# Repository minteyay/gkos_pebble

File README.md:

# wireless GKOS chording keyboard + mouse with BLE

based on the GKOS chording standard (http://gkos.com/gkos/gkos-charset.html) with a few modifications for computer-centric usage.

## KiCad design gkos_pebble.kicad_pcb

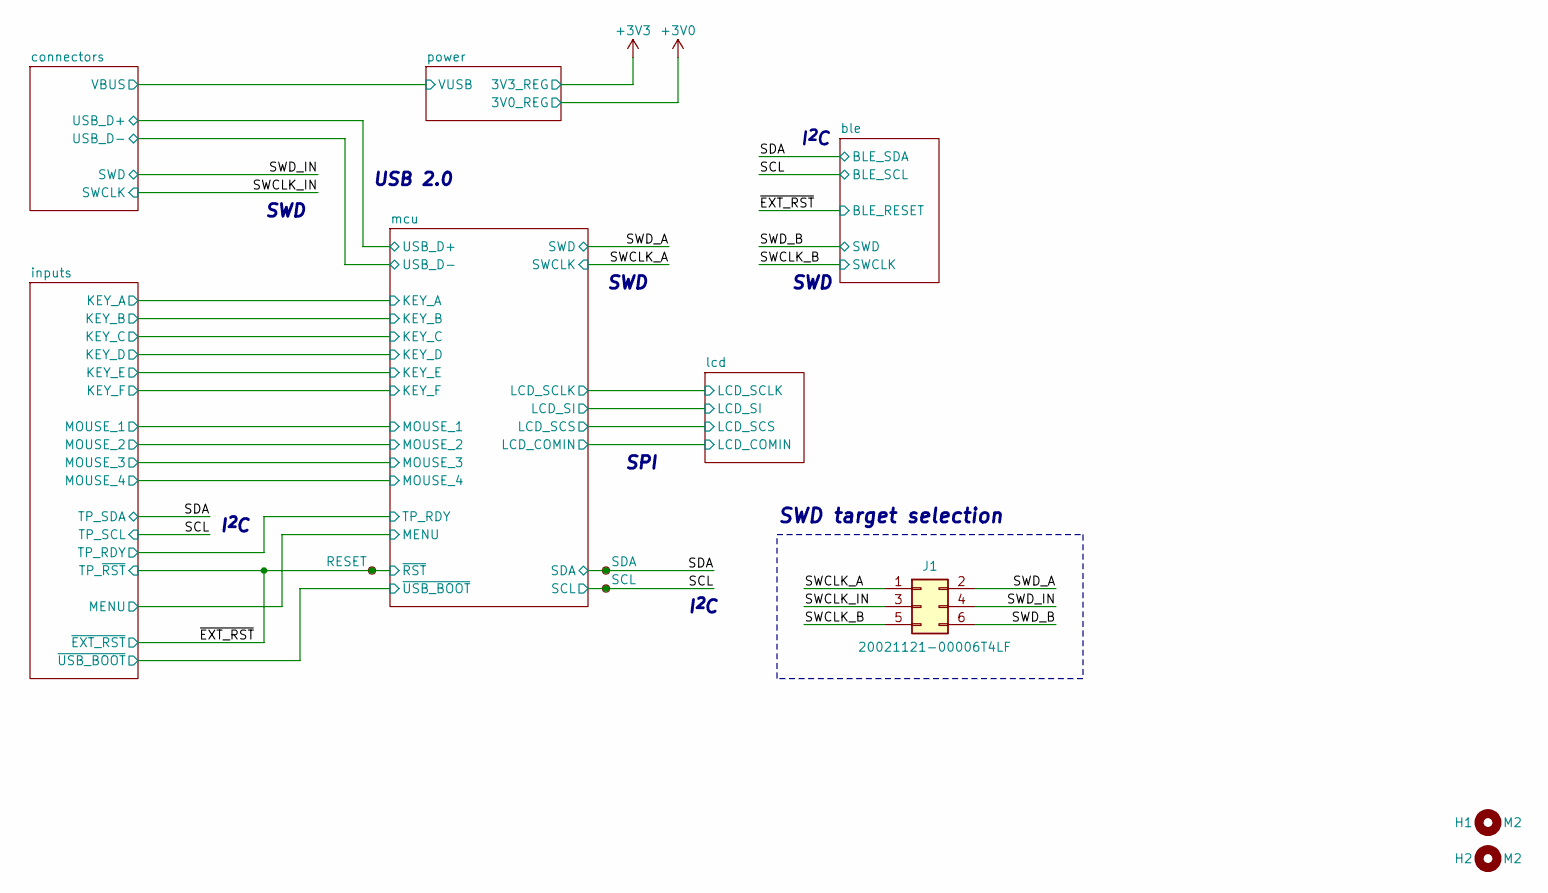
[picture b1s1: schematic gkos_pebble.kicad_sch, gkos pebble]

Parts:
H1, H2: M2; MountingHole_2.2mm_M2
J1: 20021121-00006T4LF; PinHeader_2x03_P1.27mm_Vertical_SMD
TP1: RESET; TestPoint_Pad_D1.0mm
TP2: SDA; TestPoint_Pad_D1.0mm
TP3: SCL; TestPoint_Pad_D1.0mm

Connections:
/SCL: TP3.1; also elsewhere on the board
/SDA: TP2.1; also elsewhere on the board
/SWCLK_A: J1.1; also elsewhere on the board
/SWCLK_B: J1.5; also elsewhere on the board
/SWCLK_IN: J1.3; also elsewhere on the board
/SWD_A: J1.2; also elsewhere on the board
/SWD_B: J1.6; also elsewhere on the board
/SWD_IN: J1.4; also elsewhere on the board
/~EXT_RST: TP1.1; also elsewhere on the board

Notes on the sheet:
SWD
I^{2}C
SPI
USB 2.0
SWD target selection

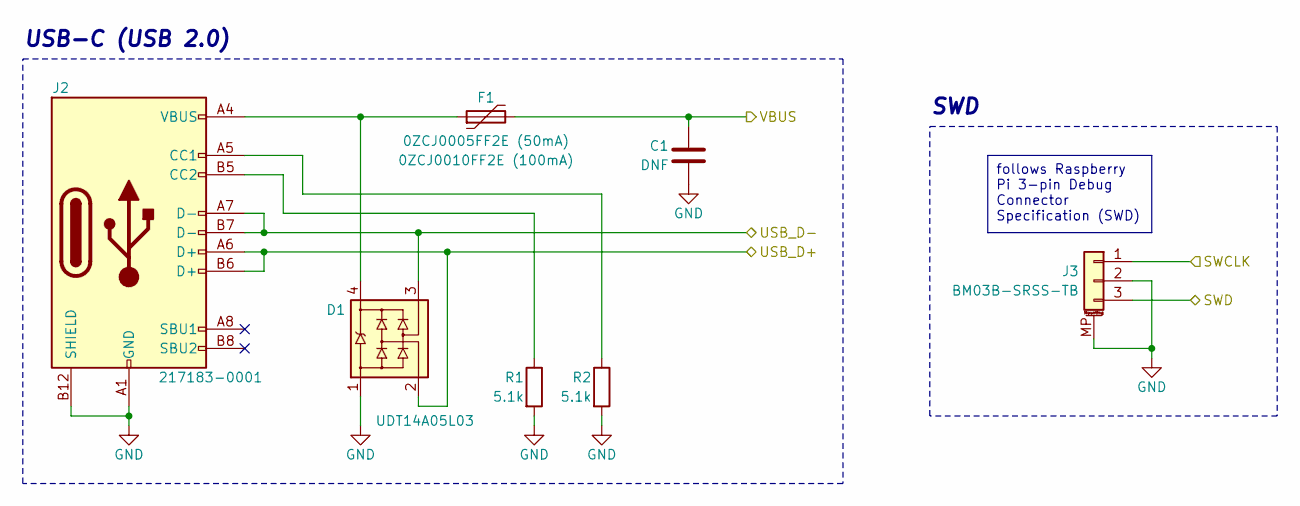
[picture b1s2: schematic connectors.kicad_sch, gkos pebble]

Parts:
C1: DNF; C_0603_1608Metric
D1: UDT14A05L03; SOT-143_Handsoldering
F1: 0ZCJ0005FF2E (50mA); R_1206_3216Metric
J2: 217183-0001; 2171830001
J3: BM03B-SRSS-TB; JST_SH_BM03B-SRSS-TB_1x03-1MP_P1.00mm_Vertical
R1, R2: 5.1k; R_0603_1608Metric

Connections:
/SWCLK_IN: J3.1; also elsewhere on the board
/SWD_IN: J3.3; also elsewhere on the board
/connectors/VBUS: C1.1, F1.2; also elsewhere on the board
/mcu/USB_D+: D1.2, J2.A6 (D+), J2.B6 (D+); also elsewhere on the board
/mcu/USB_D-: D1.3, J2.A7 (D-), J2.B7 (D-); also elsewhere on the board
GND: C1.2, D1.1, J2.A1 (GND), J2.A12 (GND), J2.B1 (GND), J2.B12 (GND), J3.2, J3.MP (MountPin), R1.2, R2.2; also elsewhere on the board
unnamed: D1.4, F1.1, J2.A4 (VBUS), J2.A9 (VBUS), J2.B4 (VBUS), J2.B9 (VBUS)
unnamed: J2.A5 (CC1), R2.1
unnamed: J2.B5 (CC2), R1.1

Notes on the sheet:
follows Raspberry Pi 3-pin Debug Connector Specification (SWD)
SWD
USB-C (USB 2.0)

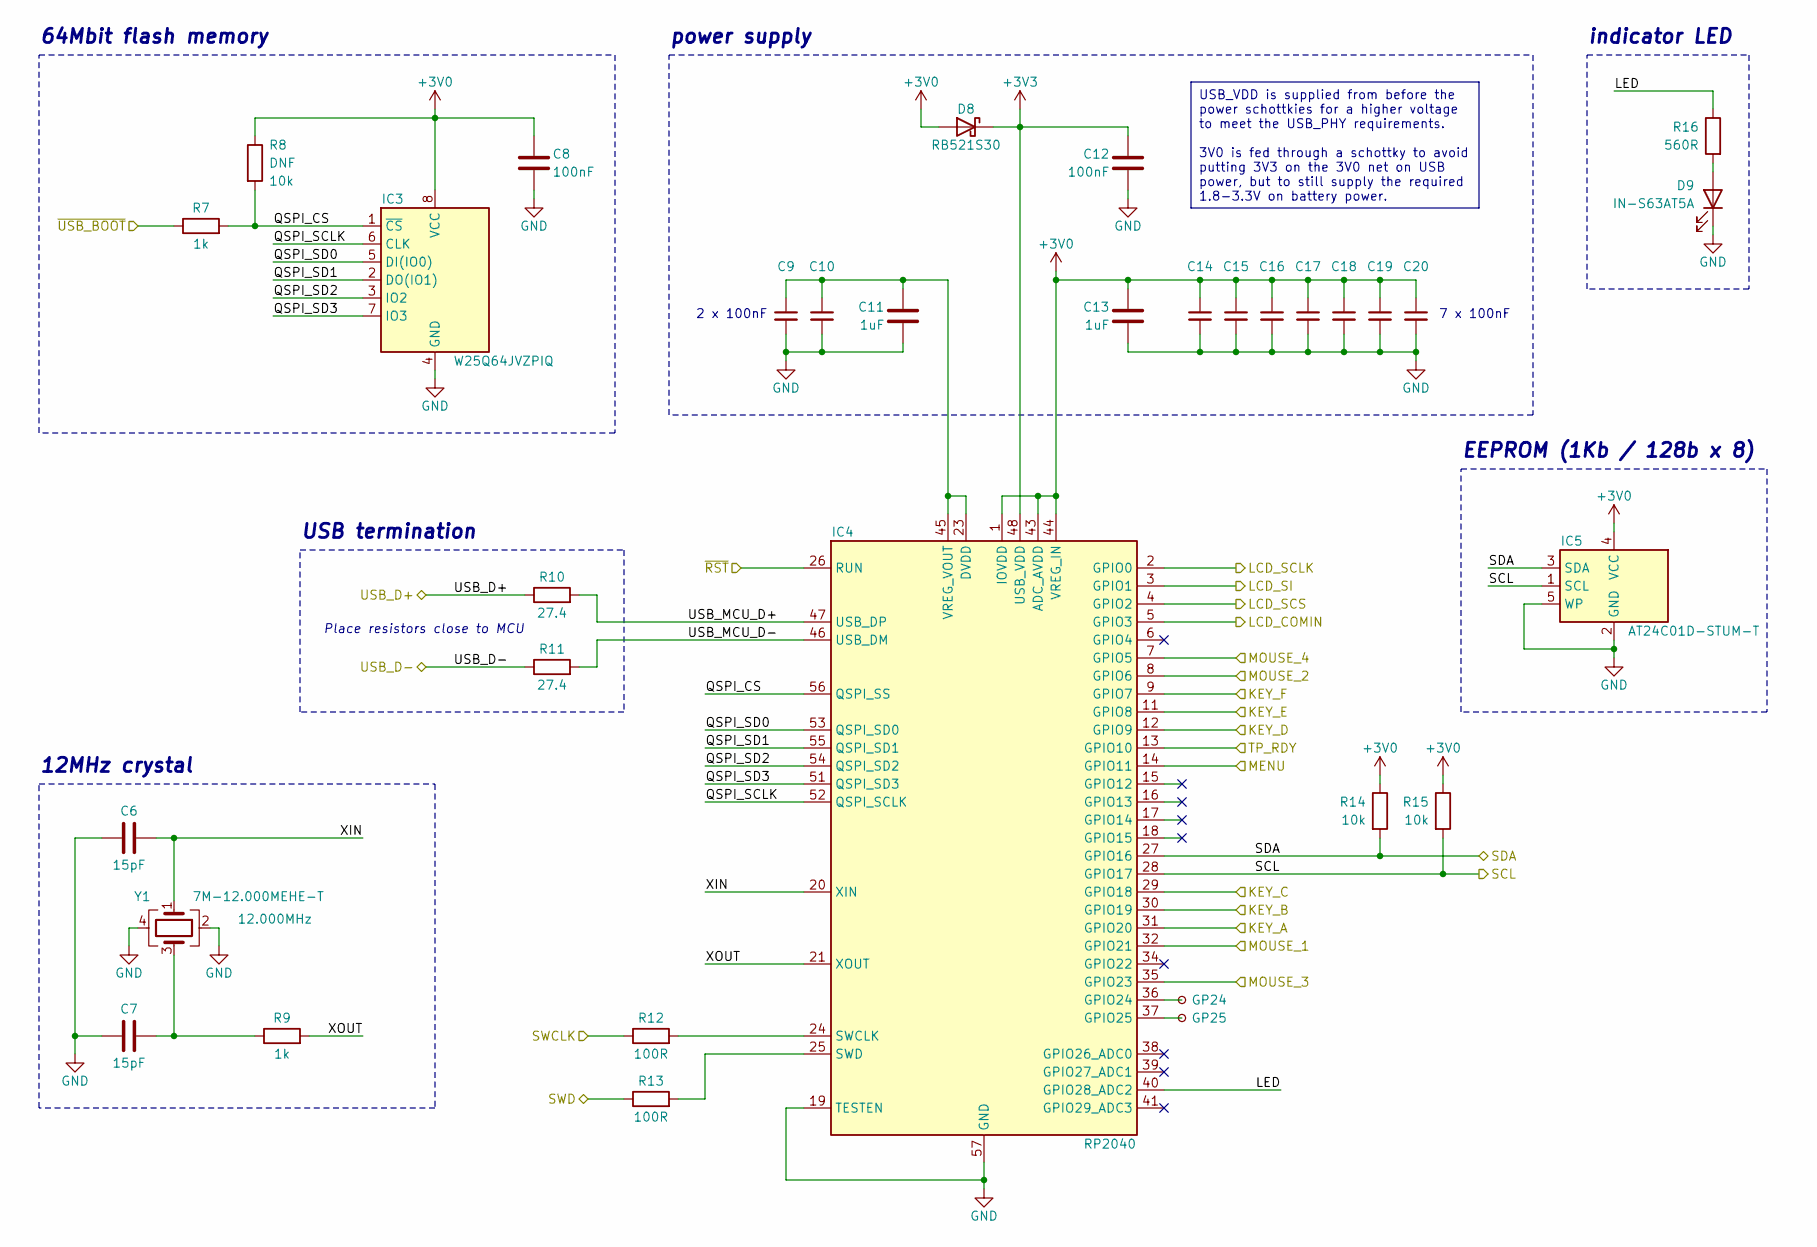
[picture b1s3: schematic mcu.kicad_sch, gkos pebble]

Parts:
C6, C7: 15pF; C_0402_1005Metric
C8: 100nF; C_0603_1608Metric
C9, C10, C12, C14, C15, C16, C17, C18, C19, C20: 100nF; C_0402_1005Metric
C11, C13: 1uF; C_0402_1005Metric
D8: RB521S30; D_SOD-523
D9: IN-S63AT5A; LED_0603_1608Metric
IC3: W25Q64JVZPIQ; WSON-8-1EP_6x5mm_P1.27mm_EP3.4x4.3mm
IC4: RP2040; QFN-56-1EP_7x7mm_P0.4mm_EP3.2x3.2mm
IC5: AT24C01D-STUM-T; SOT-23-5
R7: 1k; R_0603_1608Metric
R8: DNF; R_0603_1608Metric
R9: 1k; R_0402_1005Metric
R10, R11: 27.4; R_0402_1005Metric
R12, R13: 100R; R_0402_1005Metric
R14, R15: 10k; R_0402_1005Metric
R16: 560R; R_0603_1608Metric
TP4: GP24; TestPoint_Pad_D1.0mm
TP5: GP25; TestPoint_Pad_D1.0mm
Y1: 7M-12.000MEHE-T

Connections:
+3V0: C8.1, C13.1, C14.1, C15.1, C16.1, C17.1, C18.1, C19.1, C20.1, D8.2 (A), IC3.8 (VCC), IC4.1 (IOVDD), IC4.10 (IOVDD), IC4.22 (IOVDD), IC4.33 (IOVDD), IC4.42 (IOVDD), IC4.43 (ADC_AVDD), IC4.44 (VREG_IN), IC4.49 (IOVDD), IC5.4 (VCC), R8.1, R14.1, R15.1; also elsewhere on the board
+3V3: C12.1, D8.1 (K), IC4.48 (USB_VDD); also elsewhere on the board
/SCL: IC4.28 (GPIO17), IC5.1 (SCL), R15.2; also elsewhere on the board
/SDA: IC4.27 (GPIO16), IC5.3 (SDA), R14.2; also elsewhere on the board
/SWCLK_A: R12.1; also elsewhere on the board
/SWD_A: R13.1; also elsewhere on the board
/inputs/KEY_A: IC4.31 (GPIO20); also elsewhere on the board
/inputs/KEY_B: IC4.30 (GPIO19); also elsewhere on the board
/inputs/KEY_C: IC4.29 (GPIO18); also elsewhere on the board
/inputs/KEY_D: IC4.12 (GPIO9); also elsewhere on the board
/inputs/KEY_E: IC4.11 (GPIO8); also elsewhere on the board
/inputs/KEY_F: IC4.9 (GPIO7); also elsewhere on the board
/inputs/MENU: IC4.14 (GPIO11); also elsewhere on the board
/inputs/MOUSE_1: IC4.32 (GPIO21); also elsewhere on the board
/inputs/MOUSE_2: IC4.8 (GPIO6); also elsewhere on the board
/inputs/MOUSE_3: IC4.35 (GPIO23); also elsewhere on the board
/inputs/MOUSE_4: IC4.7 (GPIO5); also elsewhere on the board
/inputs/TP_RDY: IC4.13 (GPIO10); also elsewhere on the board
/inputs/~USB_BOOT: R7.1; also elsewhere on the board
/lcd/LCD_COMIN: IC4.5 (GPIO3); also elsewhere on the board
/lcd/LCD_SCLK: IC4.2 (GPIO0); also elsewhere on the board
/lcd/LCD_SCS: IC4.4 (GPIO2); also elsewhere on the board
/lcd/LCD_SI: IC4.3 (GPIO1); also elsewhere on the board
/mcu/LED: IC4.40 (GPIO28_ADC2), R16.1
/mcu/QSPI_CS: IC3.1 (~CS), IC4.56 (QSPI_SS), R7.2, R8.2
/mcu/QSPI_SCLK: IC3.6 (CLK), IC4.52 (QSPI_SCLK)
/mcu/QSPI_SD0: IC3.5 (DI(IO0)), IC4.53 (QSPI_SD0)
/mcu/QSPI_SD1: IC3.2 (DO(IO1)), IC4.55 (QSPI_SD1)
/mcu/QSPI_SD2: IC3.3 (IO2), IC4.54 (QSPI_SD2)
/mcu/QSPI_SD3: IC3.7 (IO3), IC4.51 (QSPI_SD3)
/mcu/USB_D+: R10.1; also elsewhere on the board
/mcu/USB_D-: R11.1; also elsewhere on the board
/mcu/USB_MCU_D+: IC4.47 (USB_DP), R10.2
/mcu/USB_MCU_D-: IC4.46 (USB_DM), R11.2
/mcu/XIN: C6.2, IC4.20 (XIN), Y1.1
/mcu/XOUT: IC4.21 (XOUT), R9.2
/~EXT_RST: IC4.26 (RUN); also elsewhere on the board
GND: C6.1, C7.1, C8.2, C9.2, C10.2, C11.2, C12.2, C13.2, C14.2, C15.2, C16.2, C17.2, C18.2, C19.2, C20.2, D9.1 (K), IC3.4 (GND), IC4.19 (TESTEN), IC4.57 (GND), IC5.2 (GND), IC5.5 (WP), Y1.2, Y1.4; also elsewhere on the board
unnamed: C7.2, R9.1, Y1.3
unnamed: D9.2 (A), R16.2
unnamed: IC4.36 (GPIO24), TP4.1
unnamed: IC4.37 (GPIO25), TP5.1
unnamed: IC4.24 (SWCLK), R12.2
unnamed: IC4.25 (SWD), R13.2
unnamed: C9.1, C10.1, C11.1, IC4.23 (DVDD), IC4.45 (VREG_VOUT), IC4.50 (DVDD)

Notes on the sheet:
USB_VDD is supplied from before the power schottkies for a higher voltage to meet the USB_PHY requirements. 3V0 is fed through a schottky to avoid putting 3V3 on the 3V0 net on USB power, but to still supply the required 1.8-3.3V on battery power.
Place resistors close to MCU
7 x 100nF
2 x 100nF
EEPROM (1Kb / 128b x 8)
indicator LED
USB termination
64Mbit flash memory
12MHz crystal
power supply

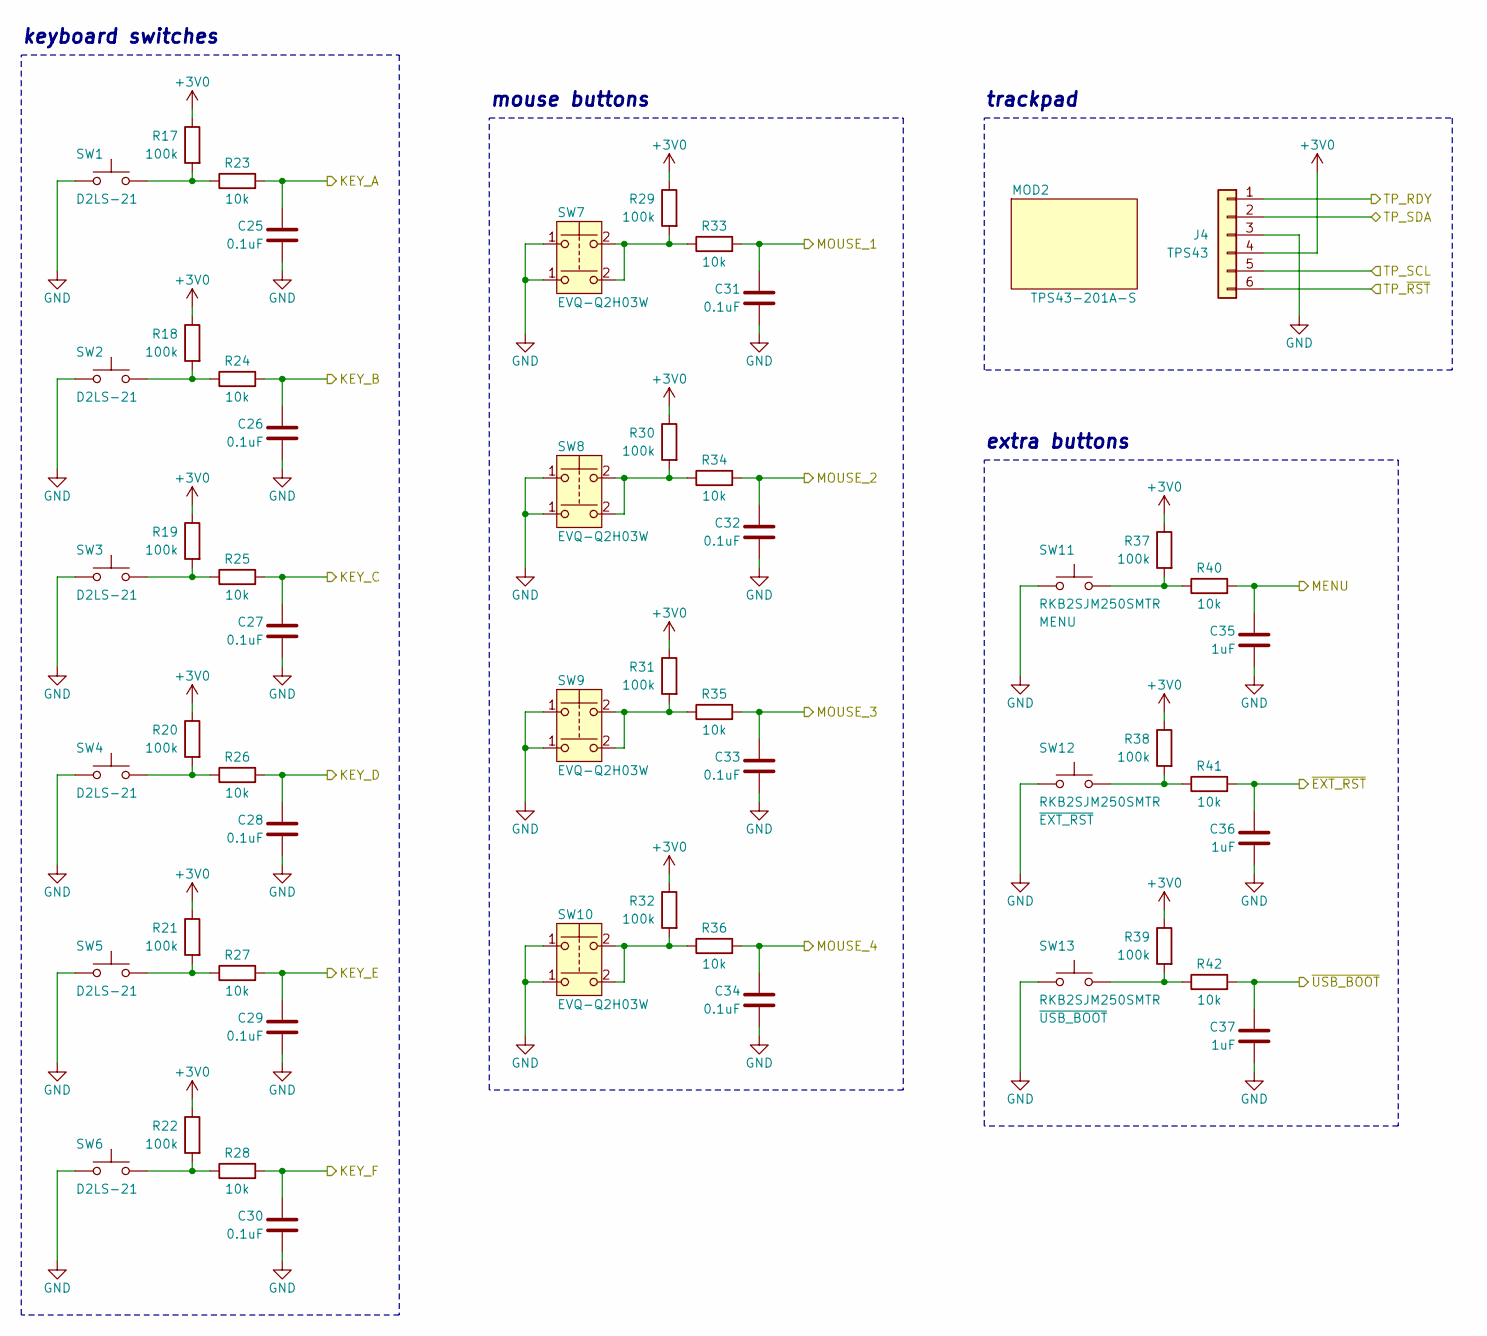
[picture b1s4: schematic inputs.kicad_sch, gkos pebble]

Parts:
C25, C26, C27, C28, C29, C30, C31, C32, C33, C34: 0.1uF; C_0603_1608Metric
C35, C36, C37: 1uF; C_0603_1608Metric
J4: TPS43; TPS43_wires
MOD2: TPS43-201A-S; TPS43
R17, R18, R19, R20, R21, R22, R29, R30, R31, R32, R37, R38, R39: 100k; R_0603_1608Metric
R23, R24, R25, R26, R27, R28, R33, R34, R35, R36, R40, R41, R42: 10k; R_0603_1608Metric
SW1, SW2, SW3, SW4, SW5, SW6: D2LS-21; D2LS
SW7, SW8, SW9, SW10: EVQ-Q2H03W
SW11, SW12, SW13: RKB2SJM250SMTR; RKB2SJM250SMTRLFS

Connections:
+3V0: J4.4, R17.1, R18.1, R19.1, R20.1, R21.1, R22.1, R29.1, R30.1, R31.1, R32.1, R37.1, R38.1, R39.1; also elsewhere on the board
/SCL: J4.5; also elsewhere on the board
/SDA: J4.2; also elsewhere on the board
/inputs/KEY_A: C25.1, R23.2; also elsewhere on the board
/inputs/KEY_B: C26.1, R24.2; also elsewhere on the board
/inputs/KEY_C: C27.1, R25.2; also elsewhere on the board
/inputs/KEY_D: C28.1, R26.2; also elsewhere on the board
/inputs/KEY_E: C29.1, R27.2; also elsewhere on the board
/inputs/KEY_F: C30.1, R28.2; also elsewhere on the board
/inputs/MENU: C35.1, R40.2; also elsewhere on the board
/inputs/MOUSE_1: C31.1, R33.2; also elsewhere on the board
/inputs/MOUSE_2: C32.1, R34.2; also elsewhere on the board
/inputs/MOUSE_3: C33.1, R35.2; also elsewhere on the board
/inputs/MOUSE_4: C34.1, R36.2; also elsewhere on the board
/inputs/TP_RDY: J4.1; also elsewhere on the board
/inputs/~USB_BOOT: C37.1, R42.2; also elsewhere on the board
/~EXT_RST: C36.1, J4.6, R41.2; also elsewhere on the board
GND: C25.2, C26.2, C27.2, C28.2, C29.2, C30.2, C31.2, C32.2, C33.2, C34.2, C35.2, C36.2, C37.2, J4.3, SW1.1, SW2.1, SW3.1, SW4.1, SW5.1, SW6.1, SW7.1 (1b), SW8.1 (1b), SW9.1 (1a), SW10.1 (1a), SW11.1, SW12.1, SW13.1; also elsewhere on the board
unnamed: R17.2, R23.1, SW1.2
unnamed: R18.2, R24.1, SW2.2
unnamed: R19.2, R25.1, SW3.2
unnamed: R20.2, R26.1, SW4.2
unnamed: R21.2, R27.1, SW5.2
unnamed: R22.2, R28.1, SW6.2
unnamed: R37.2, R40.1, SW11.2
unnamed: R38.2, R41.1, SW12.2
unnamed: R39.2, R42.1, SW13.2
unnamed: R29.2, R33.1, SW7.2 (2a)
unnamed: R30.2, R34.1, SW8.2 (2a)
unnamed: R31.2, R35.1, SW9.2 (2a)
unnamed: R32.2, R36.1, SW10.2 (2a)

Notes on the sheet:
mouse buttons
trackpad
extra buttons
keyboard switches

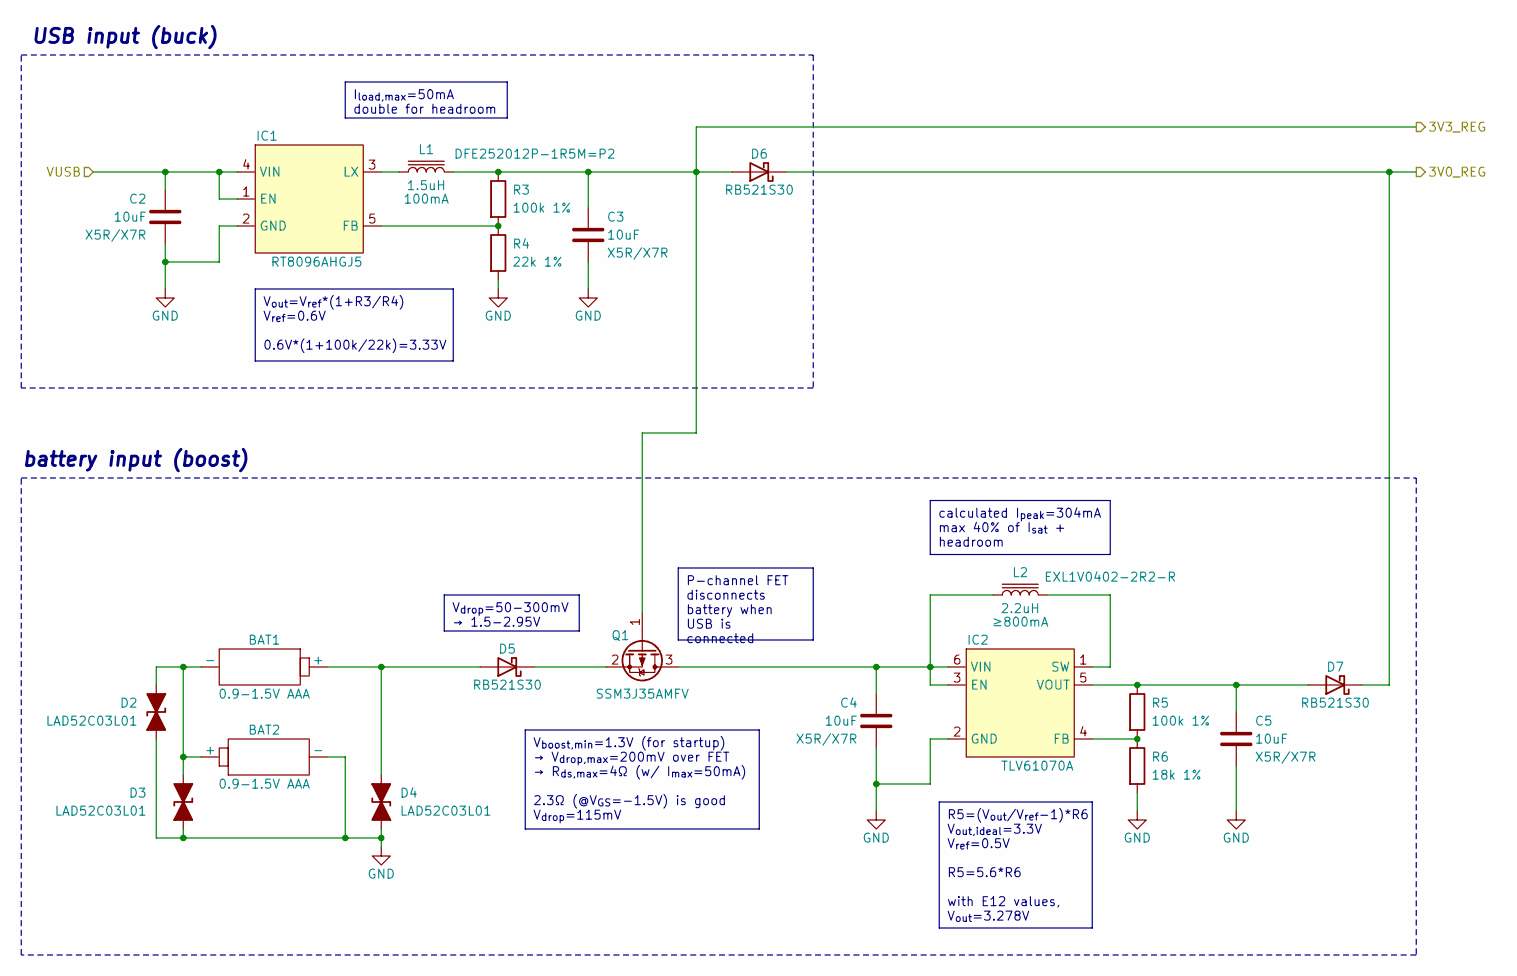
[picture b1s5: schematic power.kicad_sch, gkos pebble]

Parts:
BAT1, BAT2: 0.9-1.5V AAA; Keystone_55_1xAAA
C2, C3, C4, C5: 10uF; C_0603_1608Metric
D2, D3, D4: LAD52C03L01; D_SOD-523
D5, D6, D7: RB521S30; D_SOD-523
IC1: RT8096AHGJ5; SOT-23-5
IC2: TLV61070A; SOT-23-6
L1: 1.5uH; L_1008_2520Metric
L2: 2.2uH; EXL1V0402-2R2-R
Q1: SSM3J35AMFV; SOT-723
R3, R5: 100k 1%; R_0603_1608Metric
R4: 22k 1%; R_0603_1608Metric
R6: 18k 1%; R_0603_1608Metric

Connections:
+3V0: D6.1 (K), D7.1 (K); also elsewhere on the board
+3V3: C3.1, D6.2 (A), L1.2, Q1.1 (G), R3.1; also elsewhere on the board
/connectors/VBUS: C2.1, IC1.1 (EN), IC1.4 (VIN); also elsewhere on the board
GND: BAT2.2 (-), C2.2, C3.2, C4.2, C5.2, D2.1 (A1), D3.1 (A1), D4.1 (A1), IC1.2 (GND), IC2.2 (GND), R4.2, R6.2; also elsewhere on the board
unnamed: BAT1.1 (+), D4.2 (A2), D5.2 (A)
unnamed: BAT1.2 (-), BAT2.1 (+), D2.2 (A2), D3.2 (A2)
unnamed: D5.1 (K), Q1.2 (S)
unnamed: C5.1, D7.2 (A), IC2.5 (VOUT), R5.1
unnamed: IC1.5 (FB), R3.2, R4.1
unnamed: IC1.3 (LX), L1.1
unnamed: C4.1, IC2.3 (EN), IC2.6 (VIN), L2.1, Q1.3 (D)
unnamed: IC2.4 (FB), R5.2, R6.1
unnamed: IC2.1 (SW), L2.2

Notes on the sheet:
I_{load,max}=50mA double for headroom
P-channel FET disconnects battery when USB is connected
R5=(V_{out}/V_{ref}-1)*R6 V_{out,ideal}=3.3V V_{ref}=0.5V R5=5.6*R6 with E12 values, V_{out}=3.278V
V_{out}=V_{ref}*(1+R3/R4) V_{ref}=0.6V 0.6V*(1+100k/22k)=3.33V
V_{boost,min}=1.3V (for startup) → V_{drop,max}=200mV over FET → R_{ds,max}=4Ω (w/ I_{max}=50mA) 2.3Ω (@V_{GS}=-1.5V) is good V_{drop}=115mV
calculated I_{peak}=304mA max 40% of I_{sat} + headroom
V_{drop}=50-300mV → 1.5-2.95V
USB input (buck)
battery input (boost)

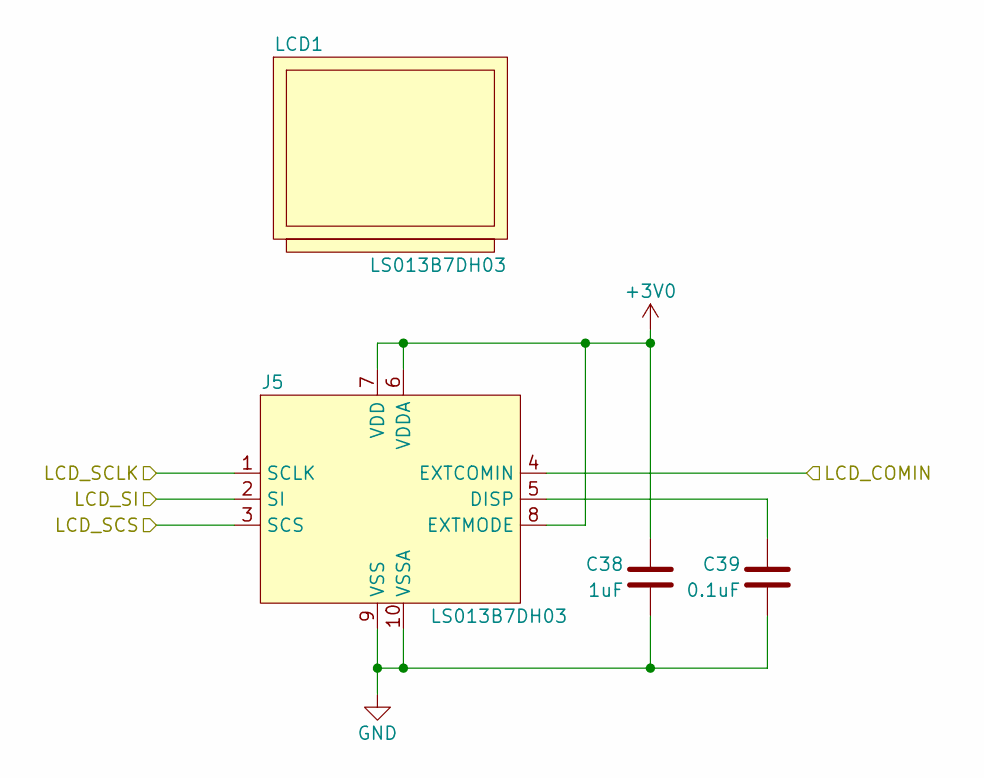
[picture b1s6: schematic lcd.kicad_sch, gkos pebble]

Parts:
C38: 1uF; C_0603_1608Metric
C39: 0.1uF; C_0603_1608Metric
J5: LS013B7DH03; F3311A7H121010E200
LCD1: LS013B7DH03

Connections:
+3V0: C38.1, J5.6 (VDDA), J5.7 (VDD), J5.8 (EXTMODE); also elsewhere on the board
/lcd/LCD_COMIN: J5.4 (EXTCOMIN); also elsewhere on the board
/lcd/LCD_SCLK: J5.1 (SCLK); also elsewhere on the board
/lcd/LCD_SCS: J5.3 (SCS); also elsewhere on the board
/lcd/LCD_SI: J5.2 (SI); also elsewhere on the board
GND: C38.2, C39.2, J5.9 (VSS), J5.10 (VSSA); also elsewhere on the board
unnamed: C39.1, J5.5 (DISP)

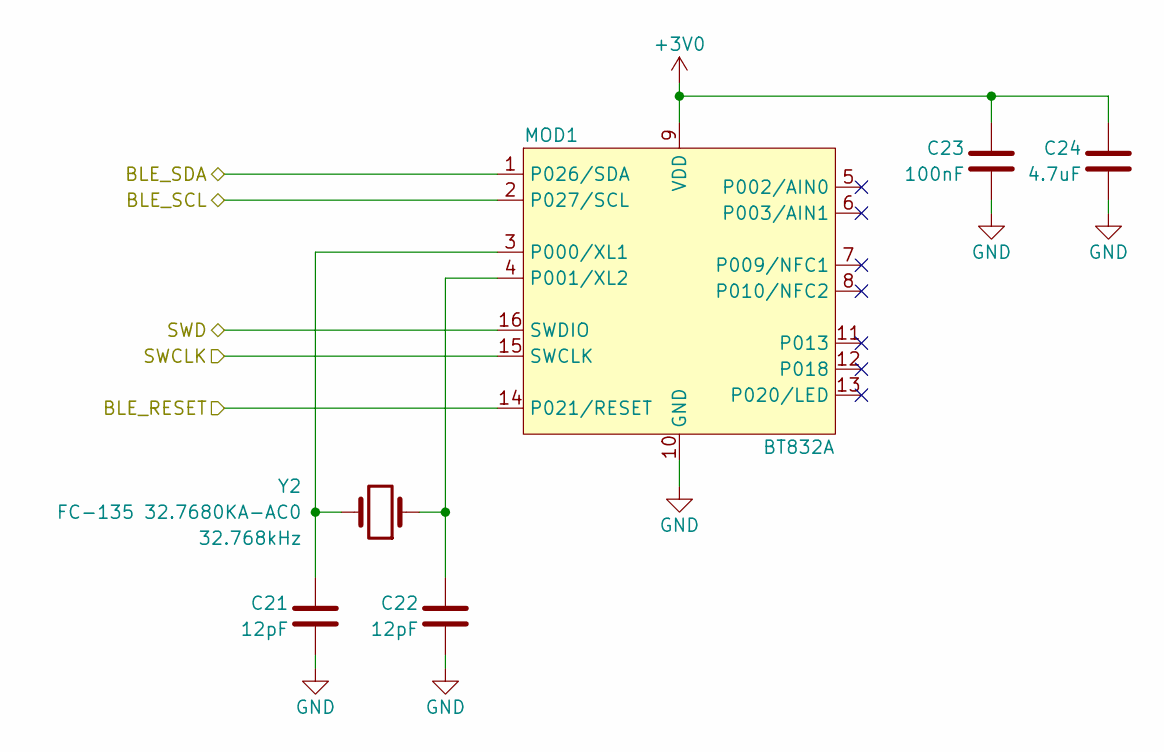
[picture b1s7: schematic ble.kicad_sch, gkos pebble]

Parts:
C21, C22: 12pF; C_0603_1608Metric
C23: 100nF; C_0603_1608Metric
C24: 4.7uF; C_0603_1608Metric
MOD1: BT832A
Y2: FC-135 32.7680KA-AC0; Crystal_SMD_3215-2Pin_3.2x1.5mm

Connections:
+3V0: C23.1, C24.1, MOD1.9 (VDD); also elsewhere on the board
/SCL: MOD1.2 (P027/SCL); also elsewhere on the board
/SDA: MOD1.1 (P026/SDA); also elsewhere on the board
/SWCLK_B: MOD1.15 (SWCLK); also elsewhere on the board
/SWD_B: MOD1.16 (SWDIO); also elsewhere on the board
/~EXT_RST: MOD1.14 (P021/RESET); also elsewhere on the board
GND: C21.1, C22.1, C23.2, C24.2, MOD1.10 (GND); also elsewhere on the board
unnamed: C21.2, MOD1.3 (P000/XL1), Y2.2
unnamed: C22.2, MOD1.4 (P001/XL2), Y2.1

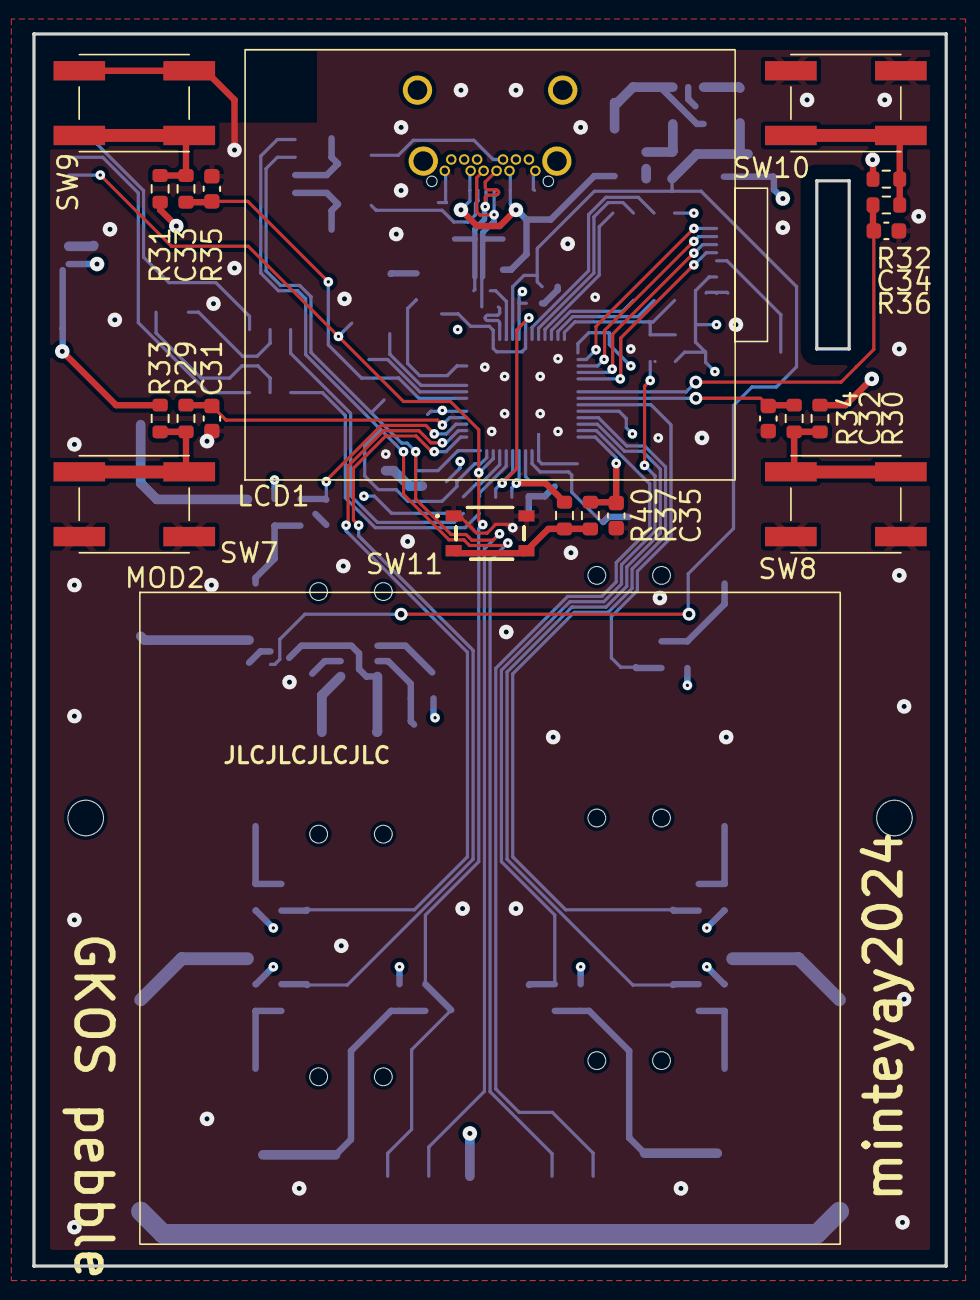
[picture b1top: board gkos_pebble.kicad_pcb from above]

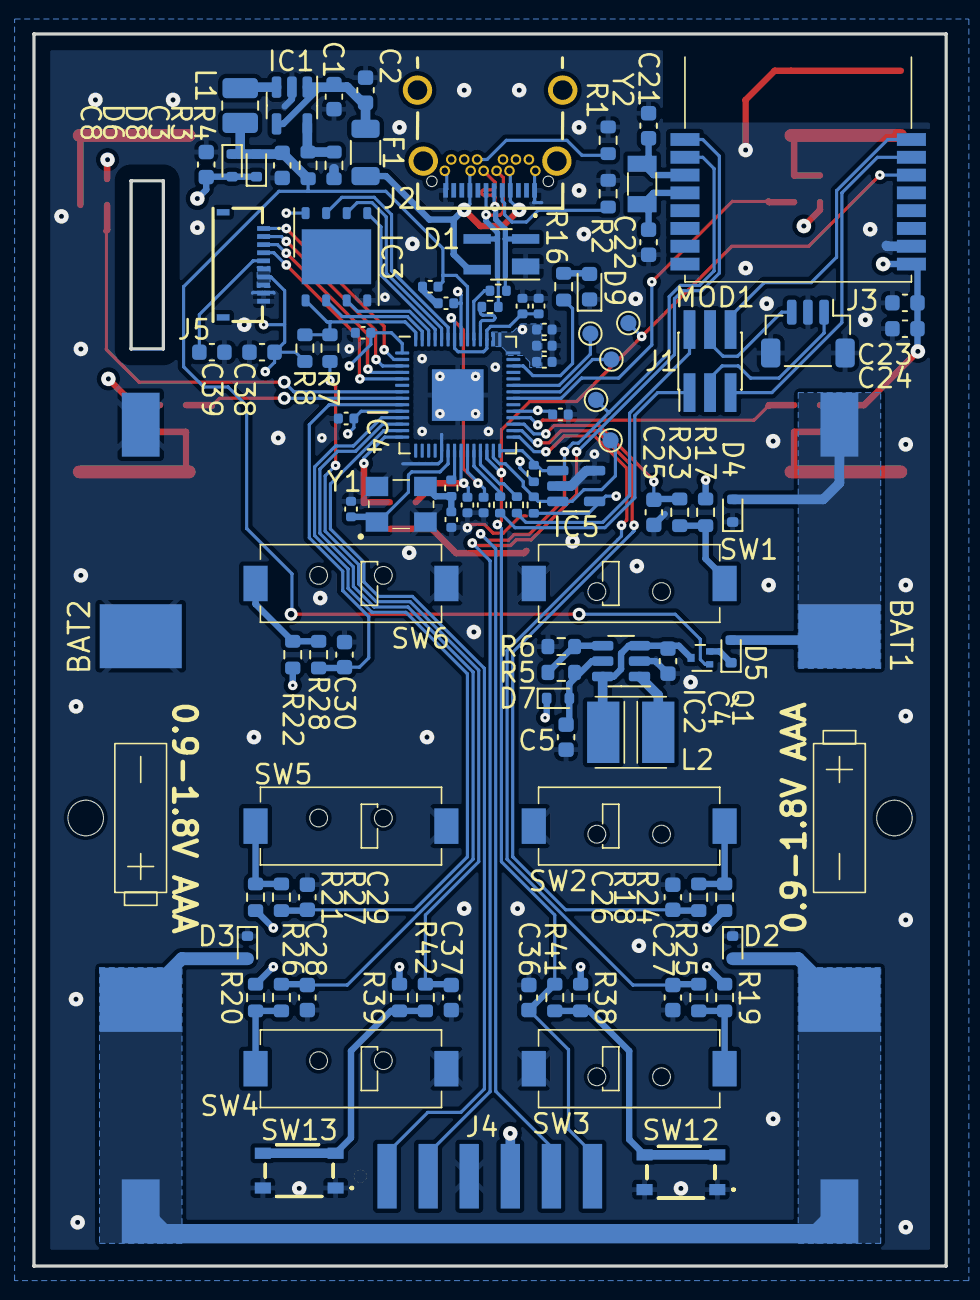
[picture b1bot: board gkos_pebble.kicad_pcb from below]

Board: 4 copper layers, 56.4 x 76.2 mm, 131 parts (107 on the bottom side), 78 nets.

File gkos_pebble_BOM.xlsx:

Itm | Qty | Reference(s) | Value | Footprint | € / unit | subtot
1 | 4 | BAT1, BAT2 | Keystone 55 | Keystone 55 x2 | 0.316 | 1.264
2 | 4 | C2, C3, C4, C5 | 10uF X5R/X7R | 0805 | 0.032000000000000001 | 0.128
3 | 2 | C6, C7 | 15pF | 0805 | 0.033000000000000002 | 0.066000000000000003
4 | 2 | C8, C23 | 100nF | 0805 | 0.012 | 0.024
5 | 10 | C9, C10, C12, C14 - C20 | 100nF | 0402 | 0.014 | 0.14000000000000001
6 | 2 | C11, C13 | 1uF | 0402 | 0.017999999999999999 | 0.035999999999999997
7 | 2 | C21, C22 | 12pF | 0805 | 0.033000000000000002 | 0.066000000000000003
8 | 1 | C24 | 4.7uF | 0805 | 0.039 | 0.039
9 | 13 | C25 - C36, C41 | 0.1uF | 0805 | 0.0089999999999999993 | 0.11699999999999999
10 | 4 | C37 - C40 | 1uF | 0805 | 0.021999999999999999 | 0.087999999999999995
11 | 1 | D1 | UDT14A05L03 | SOT-143 | 0.33500000000000002 | 0.33500000000000002
12 | 1 | D2 | LAD52C03L01 | SOD-523 | 0.29799999999999999 | 0.29799999999999999
13 | 4 | D3 - D6 | RB521S30 | SOD-523 | 0.10100000000000001 | 0.40400000000000003
14 | 1 | D7 | IN-S63AT5A | 0603 LED | 0.16500000000000001 | 0.16500000000000001
15 | 1 | F1 | 0ZCJ0005FF2E | 1206 | 0.123 | 0.123
16 | 1 | IC1 | RT8096AHGJ5 | SOT-23-5 | 0.372 | 0.372
17 | 1 | IC2 | TLV61070A | SOT-23-6 | 0.44600000000000001 | 0.44600000000000001
18 | 1 | IC3 | RP2040 | QFN-56 | 0.65000000000000002 | 0.65000000000000002
19 | 1 | J1 | 10129383-906002BLF | header 2x03 P2.54mm vert | 0.23300000000000001 | 0.23300000000000001
20 | 1 | J2 | 217183-0001 | 217183-0001 | 1.1499999999999999 | 1.1499999999999999
21 | 1 | J3 | BM03B-SRSS-TB | JST SH 1x03 P1.00mm vert | 0.48999999999999999 | 0.48999999999999999
23 | 1 | J5 | F3311A7H121010E200 | F3311A7H121010E200 | 0.39100000000000001 | 0.39100000000000001
24 | 1 | L1 | 1.5uH (DFE252012P-1R5M=P2) | 1008 inductor | 0.26000000000000001 | 0.26000000000000001
25 | 1 | L2 | 2.2uH (SRP7028AA-2R2M) | 7.3x6.6mm inductor | 0.85599999999999998 | 0.85599999999999998
26 | 1 | LCD1 | LS013B7DH03 | LS013B7DH03 | 11 | 11
27 | 1 | MOD1 | BT832A | BT832A | 6.4800000000000004 | 6.4800000000000004
28 | 1 | MOD2 | TPS43-201A-S | TPS43-201A-S | 4.2800000000000002 | 4.2800000000000002
29 | 1 | Q1 | SSM3J35AMFV | SOT-723 | 0.214 | 0.214
30 | 2 | R1, R2 | 5.1k | 0805 | 0.014999999999999999 | 0.029999999999999999
31 | 2 | R3, R5 | 100k 1% | 0805 | 0.159 | 0.318
32 | 1 | R4 | 22k 1% | 0805 | 0.019 | 0.019
33 | 1 | R6 | 18k 1% | 0805 | 0.014999999999999999 | 0.014999999999999999
34 | 2 | R7, R9 | 1k | 0805 | 0.014999999999999999 | 0.029999999999999999
35 | 2 | R10, R11 | 27R4 | 0402 | 0.016 | 0.032000000000000001
36 | 2 | R12, R13 | 100R | 0402 | 0.01 | 0.02
37 | 17 | R14, R15, R23 - R28, R35 - R40, R44 - R46 | 10k | 0805 | 0.010999999999999999 | 0.187
38 | 1 | R16 | 560R | 0805 | 0.01 | 0.01
39 | 15 | R17 - R22, R29 - R34, R41 - R43 | 100k | 0805 | 0.0089999999999999993 | 0.13499999999999998
40 | 6 | SW1 - SW6 | CPG135001D02 (Kailh Choc) | CPG135001D02 | 1.03 | 6.1799999999999997
41 | 6 | SW7 - SW12 | D2F-01F | D2F-01F | 0.59999999999999998 | 3.5999999999999996
42 | 3 | SW13 - SW15 | RKB2SJM250SMTR LFS | RKB2SJM250SMTR LFS | 0.17699999999999999 | 0.53099999999999992
43 | 1 | U1 | W25Q64JVSSIQ | SOIC-8 | 0.94899999999999995 | 0.94899999999999995
44 | 1 | Y1 | ABM3B-12.000MHZ-10-1-U-T | 5.0x3.2mm XTAL | 0.77200000000000002 | 0.77200000000000002
45 | 1 | Y2 | FC-135 32.7680KA-AC0 | 3.2x1.5mm XTAL | 0.55800000000000005 | 0.55800000000000005
 |  |  |  | total (EUR) |  | 43.501000000000005

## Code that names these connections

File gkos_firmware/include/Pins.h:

#pragma once
#include <Arduino.h>

namespace Pins {
    const pin_size_t KEY_A = 20;
    const pin_size_t KEY_B = 19;
    const pin_size_t KEY_C = 18;
    const pin_size_t KEY_D = 7;
    const pin_size_t KEY_E = 8;
    const pin_size_t KEY_F = 9;

    const pin_size_t MOUSE_1 = 21;
    const pin_size_t MOUSE_2 = 6;
    const pin_size_t MOUSE_3 = 23;
    const pin_size_t MOUSE_4 = 5;

    const pin_size_t SDA = 16;
    const pin_size_t SCL = 17;

    const pin_size_t LCD_COMIN = 0;
    const pin_size_t LCD_SCS = 1;
    const pin_size_t LCD_SCLK = 2;
    const pin_size_t LCD_SI = 3;

    const pin_size_t MENU = 11;

    const pin_size_t TP_RDY = 10;
    const pin_size_t TP_RST = 24;

    const pin_size_t LED = 25;
}

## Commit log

2024-02-23 create simple readme
2024-02-23 power schema
2024-03-14 big commit with power and inputs
2024-03-18 power supply cleanup and overvoltage protection
2024-03-18 added power ratings to overvoltage resistors
2024-03-23 schema functionally done
2024-03-23 reannotation
2024-03-23 change 0603 to 0805
2024-03-23 add external modules
2024-03-23 change usb buck resistor values
2024-03-23 add very approximate BOM
2024-03-23 update BOM
2024-03-25 schematic cleanup
2024-03-25 cleanup cleanup
2024-03-25 added testpoints
2024-03-25 test points
2024-03-26 new mouse button setup
2024-03-26 reannotate
2024-03-26 finish new mouse button design
2024-03-26 use all smd for mouse buttons
2024-03-26 tighter display courtyard
2024-03-26 move to smd keyboard switches
2024-03-26 GPIO shuffling
2024-03-27 add button plunger to footprint
2024-03-27 GPIO shuffling + reannotate
2024-03-27 swap flash to smaller WSON package
2024-03-27 in progress pcb
2024-03-28 schematic pdf
2024-03-29 change 2.54mm SWD header to 1.27mm
2024-03-30 add second battery TVS
2024-03-30 update schema
2024-03-30 add one more battery TVS
2024-03-30 initial component placement on pcb
2024-03-30 oops lcd had no power
2024-03-31 add the dang eeprom
2024-03-31 swap crystal for smaller one
2024-03-31 in-progress second layout attempt
2024-04-03 pcb done, also kicad 8
2024-04-06 gerbers
2024-04-06 updated BOM save for passives
2025-05-22 added arduino (PIO) firmware project
2025-06-10 basic gkos chording
2025-06-10 cleanup
